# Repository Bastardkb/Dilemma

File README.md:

---

The Dilemma is a vertical stagger low-profile keyboard with mods.

## Table of contents

- [Features](#features)
- [Versions](#versions)
- [Required components](#required-components)
  - [3d prints - cases](#3d-prints---cases)
  - [Electronics](#electronics)
  - [Procyon mod](#procyon-mod)
  - [Cirque Trackpad mod](#cirque-trackpad-mod)
  - [Cases](#cases)
    - [Acrylic midplate (v2 only)](#acrylic-midplate-v2-only)
  - [Metal plates](#metal-plates)
  - [Community mods](#community-mods)
  - [Build guide](#build-guide)
  - [Forks](#forks)

---

# Features

- heavy pinky stagger
- MX and choc compatible
- version with hotswap
- underglow RGB, per-key RGB
- 2 Rotary encoders on thumb clusters
- connectors for OLED, LCD

# Versions

There are multiple versions of the dilemma:

| Folder          | Name                   | Size  | PCBA | Trackpad | Switches         | Additional features                          |
| --------------- | ---------------------- | ----- | ---- | -------- | ---------------- | -------------------------------------------- |
| `3x5_2`         | Dilemma DIY V2         | 3x5+2 | no   | Cirque   | MX, Choc V1      |                                              |
| `3x5_3`         | Dilemma V2             | 3x5+3 | yes  | Cirque   | MX, Choc V1      | Underglow, per-key RGB, rotary encoders      |
| `3x5_3_procyon` | Dilemma V3 hotswap     | 3x5+3 | yes  | Procyon  | Choc V1, hotswap | Underglow, per-key RGB, rotary encoders, VIK |
| `4x6_4`         | Dilemma MAX            | 4x6+4 | yes  | Cirque   | MX, Choc V1      | Underglow, per-key RGB, rotary encoders      |
| `4x6_4_procyon` | Dilemma MAX V3 hotswap | 4x6+4 | yes  | Procyon  | Choc V1, hotswap | Underglow, per-key RGB, rotary encodersk VIK |

# Required components

## 3d prints - cases

You can find the required 3d prints in the `mechanical` folder.

Most cases require a transparent mid layer to look good. You can either print it, or order it cut in acrylic.

## Electronics

The new revisions are made to be PCBA'd, you can find the gerber, BOM and POS files in the [Releases](https://github.com/bastardkb/dilemma/releases) section.

## Procyon mod

The `dilemma v3 hotswap` is made to work with a [Procyon PCB](https://github.com/bstiq/procyon).

## Cirque Trackpad mod

This mod uses I2C on the DIY version, and SPI on the assembled version.

The DIY version requires removing some resistors from the trackpad:

- R1
- R7 and R8 if you are using a microcontroller that runs on 5V

When installing the trackpad mod, you will need:

| Part name           | Amount | Link / source           |
| ------------------- | ------ | ----------------------- |
| M3 screw, torx, 6mm | 4      | Conrad                  |
| M3x5x5 screw insert | 4      | Aliexpress              |
| 3d printed parts    |        | See `mechanical` folder |
| 40mm cirque trackpad, curved    |        | |

If building the PCBA version, you will also need:

| Part name                                                     | Amount | Link / source |
| ------------------------------------------------------------- | ------ | ------------- |
| 12-position FPC cable, 0.5mm pitch, same side contacts, 100mm, type-B | 1      | Farnell       |

If building the DIY version, you will also need:

| Part name               | Amount | Link / source |
| ----------------------- | ------ | ------------- |
| SOD123 Resistor, 5kOhms | 2      |               |
| Cables                  |        |               |

## Cases

### Acrylic midplate (v2 only)

This case is only compatible with the assembled_v2 version !

Add an underglow effect and a beautiful view into the PCB with those acrylic midplates.

## Metal plates

Optional metal plates enables the use of tripods through magsafe magnets.

Order the [metal plates](mechanical/plates/v2/bottom_metal.dxf) in 3mm thickness. The metal needs to be *magnetized* !
Grab the appropriate DXF from the matched folder.

You will need:

| Part name              | Amount | Details           |
| ---------------------- | ------ | ----------------- |
| Metal plates           | 2      | 3mm               |
| Tripods                | 2      | Neewer Z flex     |
| Magsafe tripod adapter | 2      | Amazon/Aliexpress |

## Community mods

There are a range of community mods available (hex plates, covers...).

You can find more information in the readme in the `mechanical/community mods` folder.

## Build guide

https://docs.bastardkb.com/bg_dilemma/intro.html

## Forks

- [3x6 version](https://github.com/bstiq/Dilemma_3x6/)
- [3x5 + 3 version](https://github.com/dixls/Dilemma-3mod)

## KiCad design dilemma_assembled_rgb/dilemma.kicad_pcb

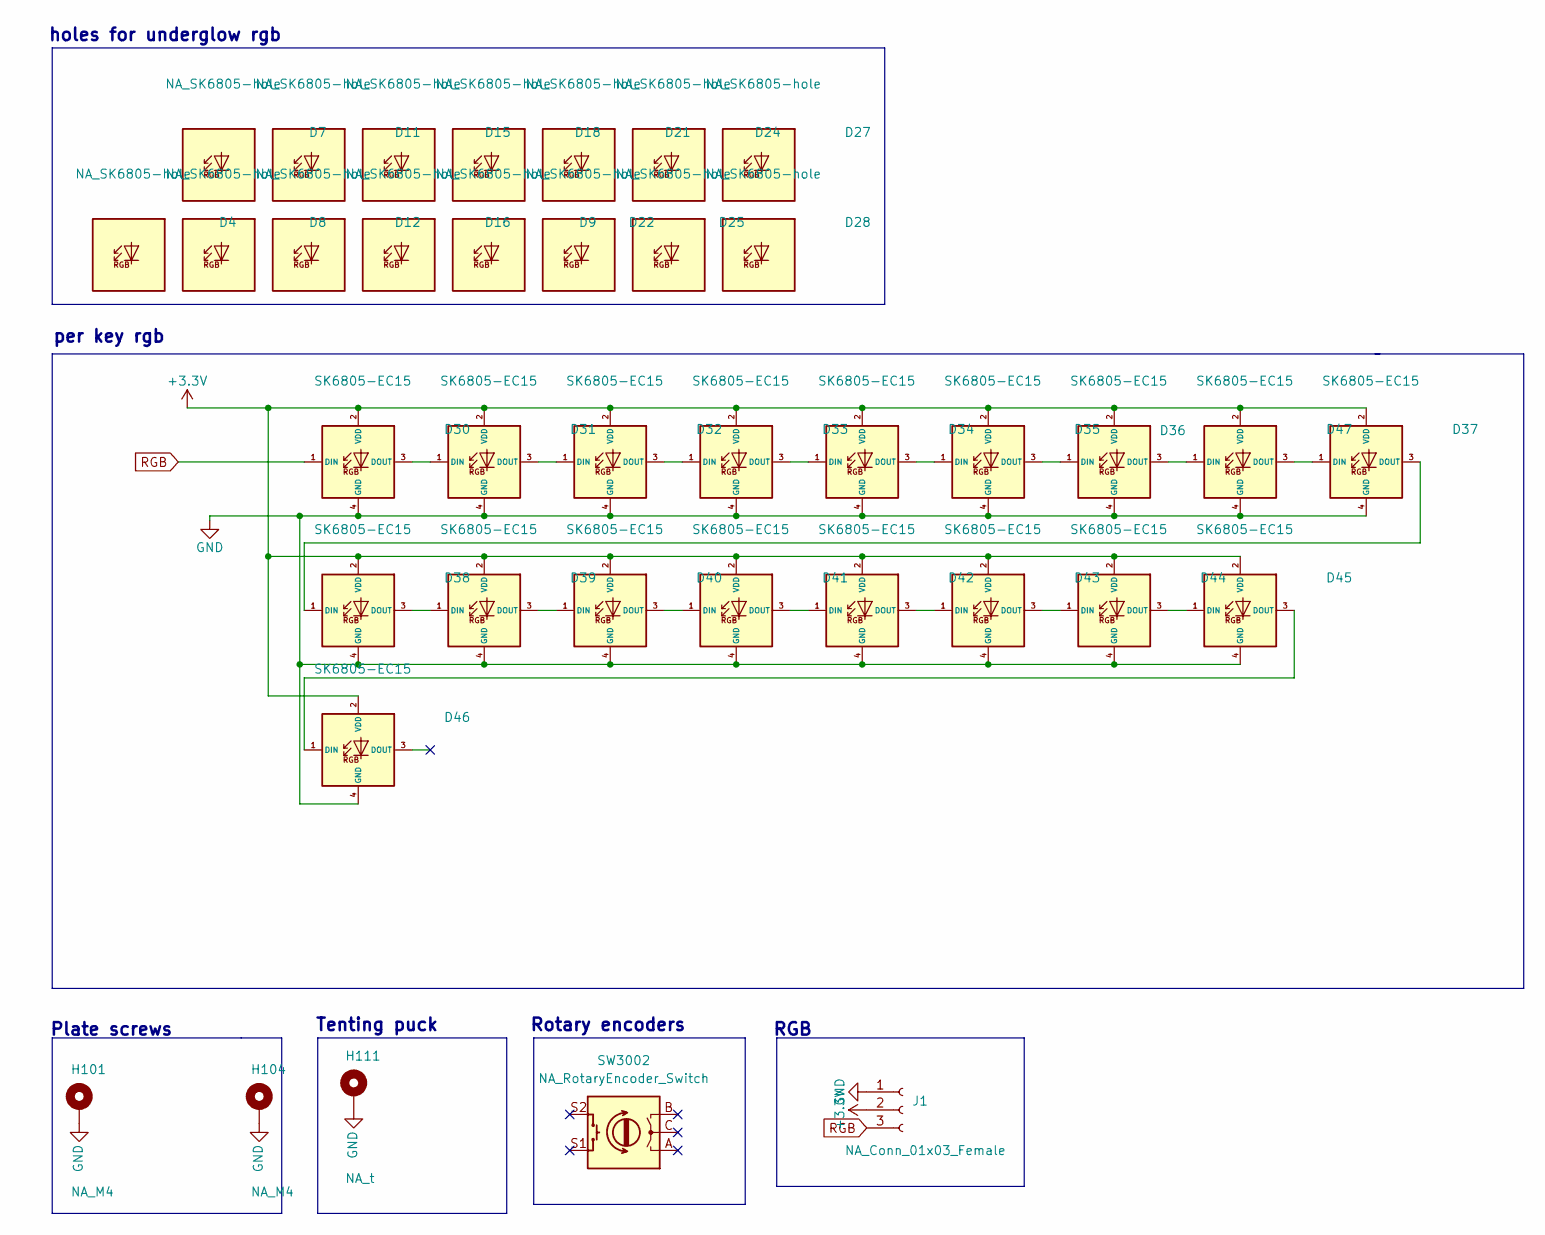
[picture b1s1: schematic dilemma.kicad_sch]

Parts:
D4, D7, D8, D21, D22, D24, D25, D27, D28: NA_SK6805-hole; LED_SK6805-EC15_1.5x1.5mm_P0.6mm_handsolder; MPN SK6805-EC15; LCSC C2890035
D9, D11, D12, D15, D16, D18: NA_SK6805-hole; LED_SK6805-EC15_hole; MPN SK6805-EC15; LCSC C2890035
D30, D31, D32, D33, D34, D35, D36, D37, D38, D39, D40, D41, D42, D43, D44, D45, D46, D47: SK6805-EC15; LED_SK6805-EC15_withSwitch; MPN SK6805-EC15; LCSC C2890035
H101, H104: NA_M4; MountingHole_3mm_Pad_hole
H111: NA_t; Tenting_Puck
J1: NA_Conn_01x03_Female; PinHeader_1x03_P2.54mm_Vertical_smd
SW3002: NA_RotaryEncoder_Switch; RotaryEncoder_Alps_EC11E-Switch_Vertical_H20mm_holes

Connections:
+3V3: D30.2 (VDD), D31.2 (VDD), D32.2 (VDD), D33.2 (VDD), D34.2 (VDD), D35.2 (VDD), D36.2 (VDD), D37.2 (VDD), D38.2 (VDD), D39.2 (VDD), D40.2 (VDD), D41.2 (VDD), D42.2 (VDD), D43.2 (VDD), D44.2 (VDD), D45.2 (VDD), D46.2 (VDD), D47.2 (VDD), J1.2
GND: D30.4 (GND), D31.4 (GND), D32.4 (GND), D33.4 (GND), D34.4 (GND), D35.4 (GND), D36.4 (GND), D37.4 (GND), D38.4 (GND), D39.4 (GND), D40.4 (GND), D41.4 (GND), D42.4 (GND), D43.4 (GND), D44.4 (GND), D45.4 (GND), D46.4 (GND), D47.4 (GND), H101.1, H104.1, H111.1, J1.1
unnamed: D30.3 (DOUT), D31.1 (DIN)
unnamed: D31.3 (DOUT), D32.1 (DIN)
unnamed: D32.3 (DOUT), D33.1 (DIN)
unnamed: D33.3 (DOUT), D34.1 (DIN)
unnamed: D34.3 (DOUT), D35.1 (DIN)
unnamed: D35.3 (DOUT), D36.1 (DIN)
unnamed: D36.3 (DOUT), D47.1 (DIN)
unnamed: D37.1 (DIN), D47.3 (DOUT)
unnamed: D37.3 (DOUT), D38.1 (DIN)
unnamed: D38.3 (DOUT), D39.1 (DIN)
unnamed: D39.3 (DOUT), D40.1 (DIN)
unnamed: D40.3 (DOUT), D41.1 (DIN)
unnamed: D41.3 (DOUT), D42.1 (DIN)
unnamed: D42.3 (DOUT), D43.1 (DIN)
unnamed: D43.3 (DOUT), D44.1 (DIN)
unnamed: D44.3 (DOUT), D45.1 (DIN)
unnamed: D45.3 (DOUT), D46.1 (DIN)
RGB: D30.1 (DIN), J1.3

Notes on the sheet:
per key rgb
Rotary encoders
RGB
holes for underglow rgb
Tenting puck
Plate screws

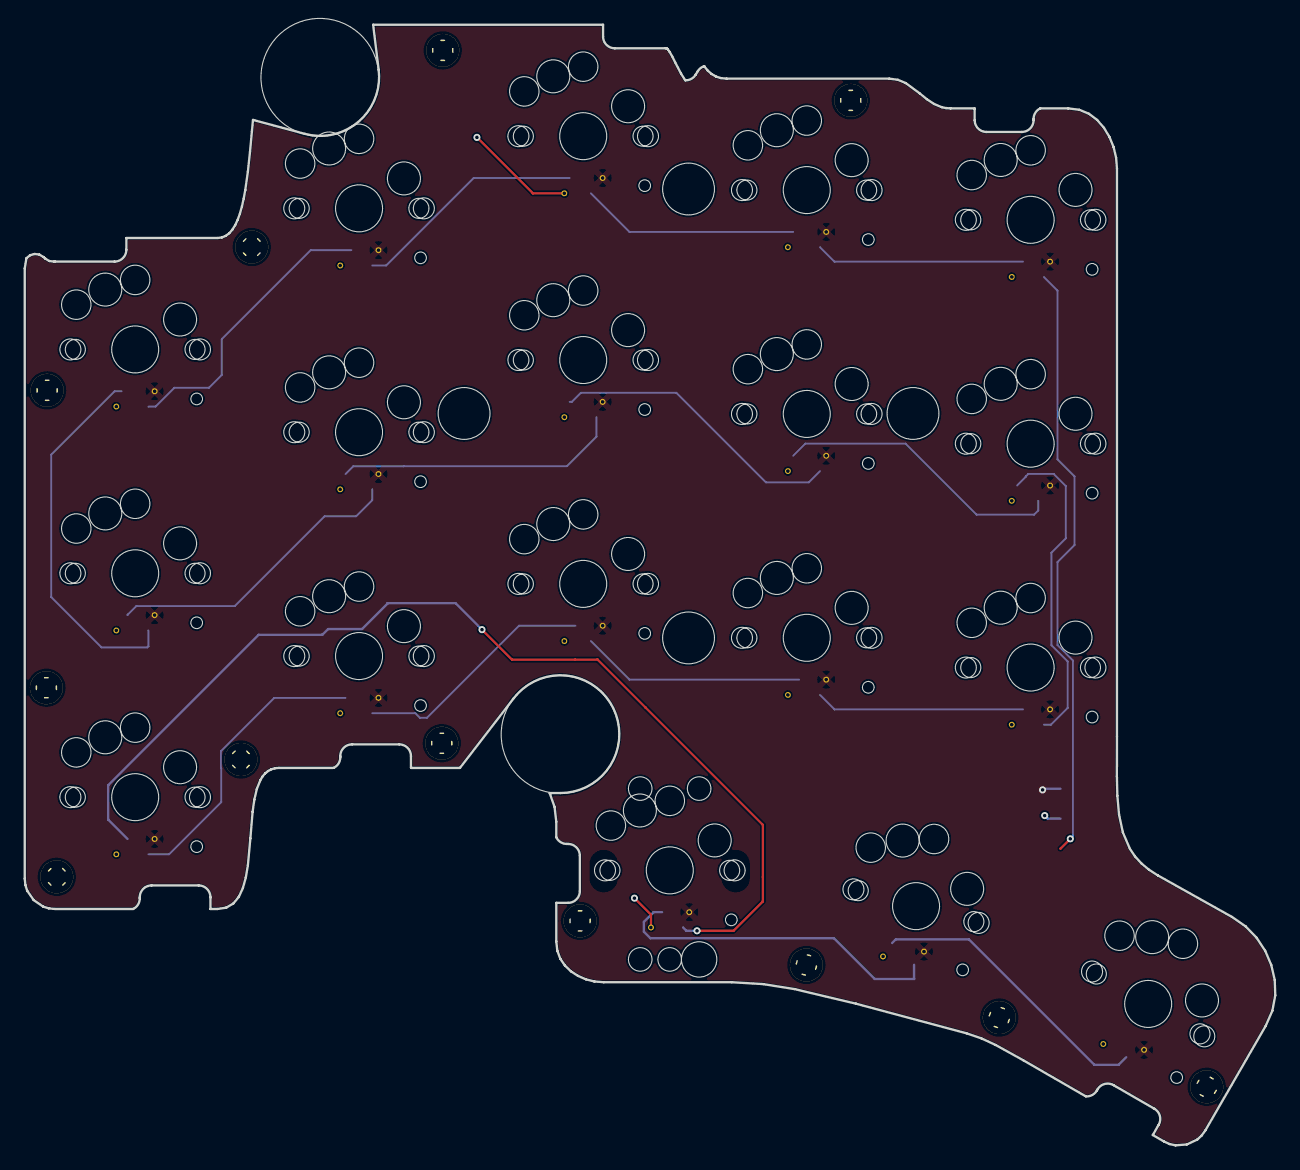
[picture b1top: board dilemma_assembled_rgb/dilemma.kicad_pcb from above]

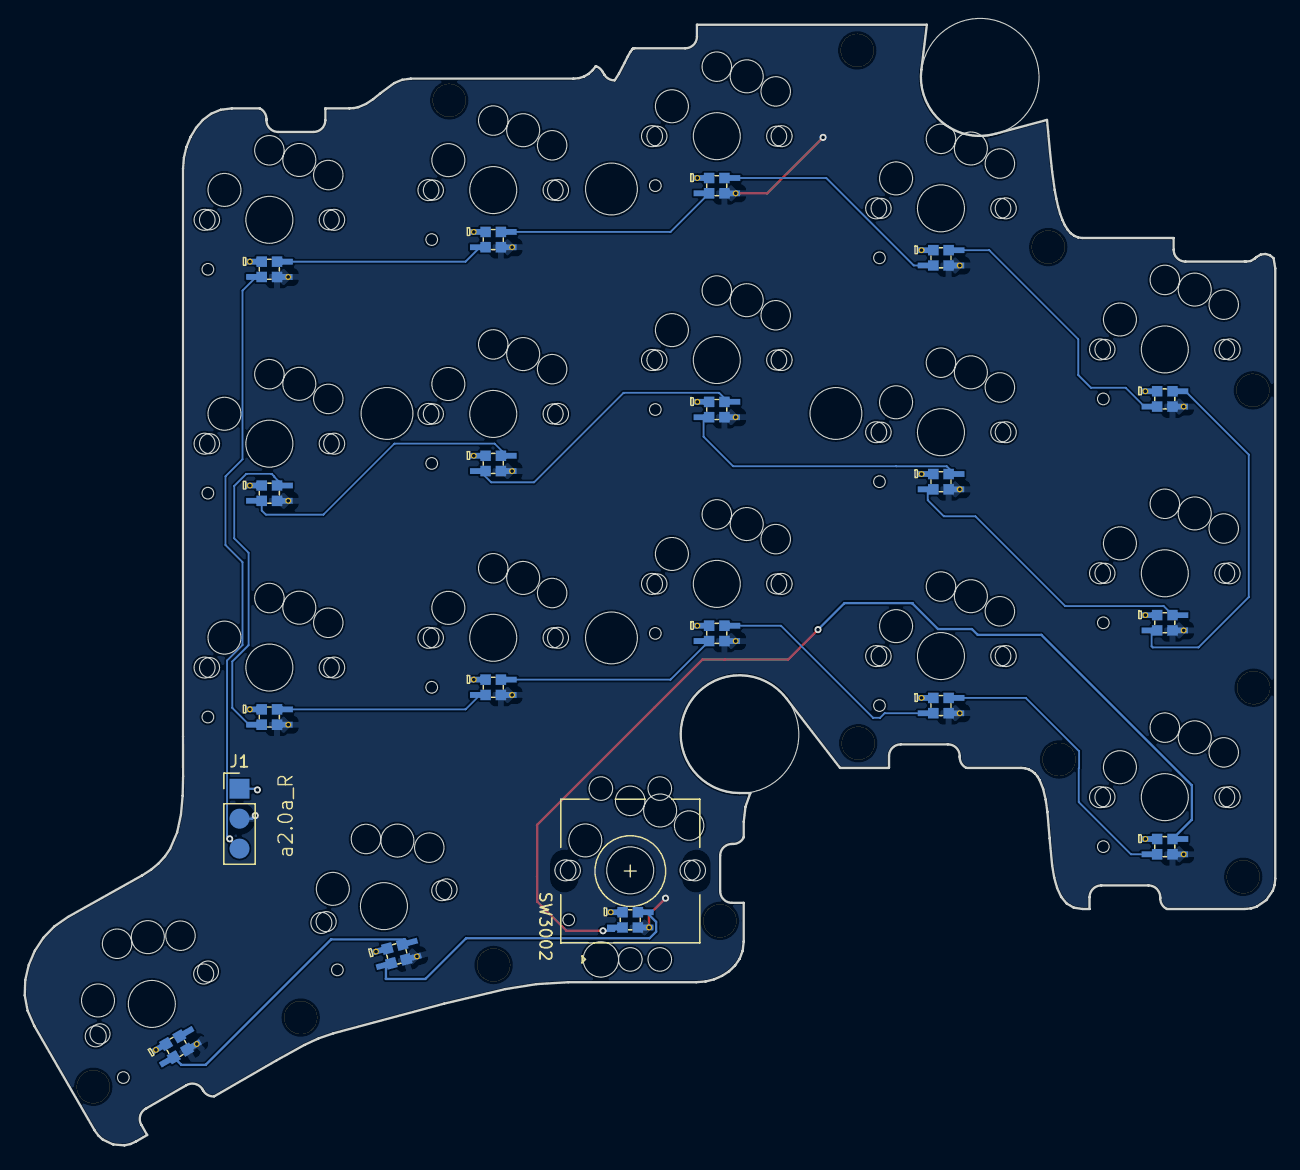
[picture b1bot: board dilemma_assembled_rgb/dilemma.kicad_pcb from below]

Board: 2 copper layers, 106.1 x 95.1 mm, 35 parts (20 on the bottom side), 20 nets.

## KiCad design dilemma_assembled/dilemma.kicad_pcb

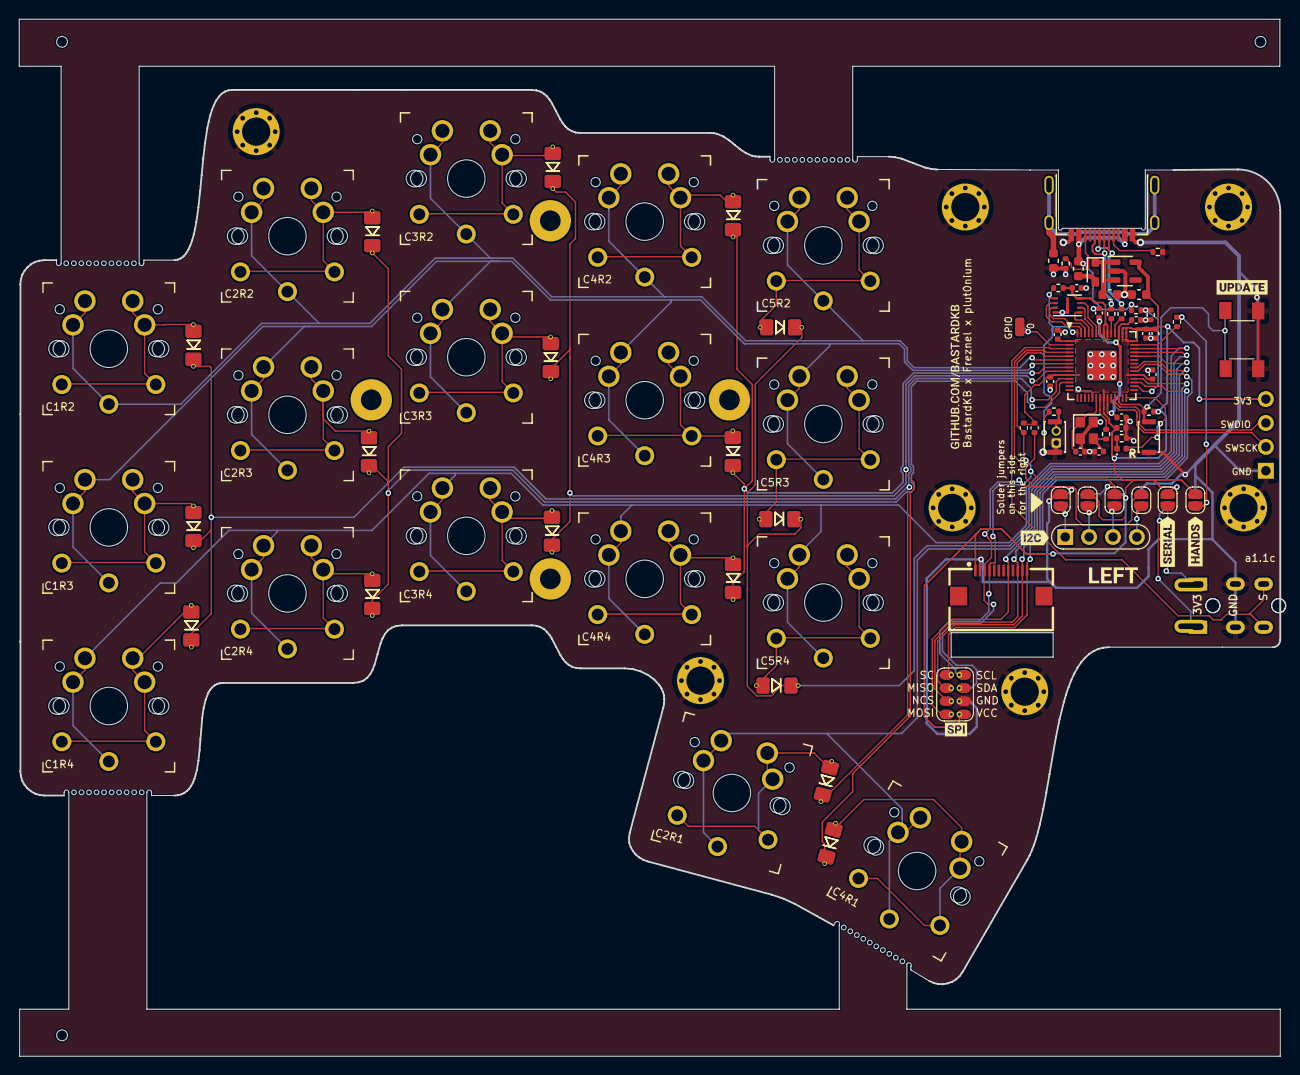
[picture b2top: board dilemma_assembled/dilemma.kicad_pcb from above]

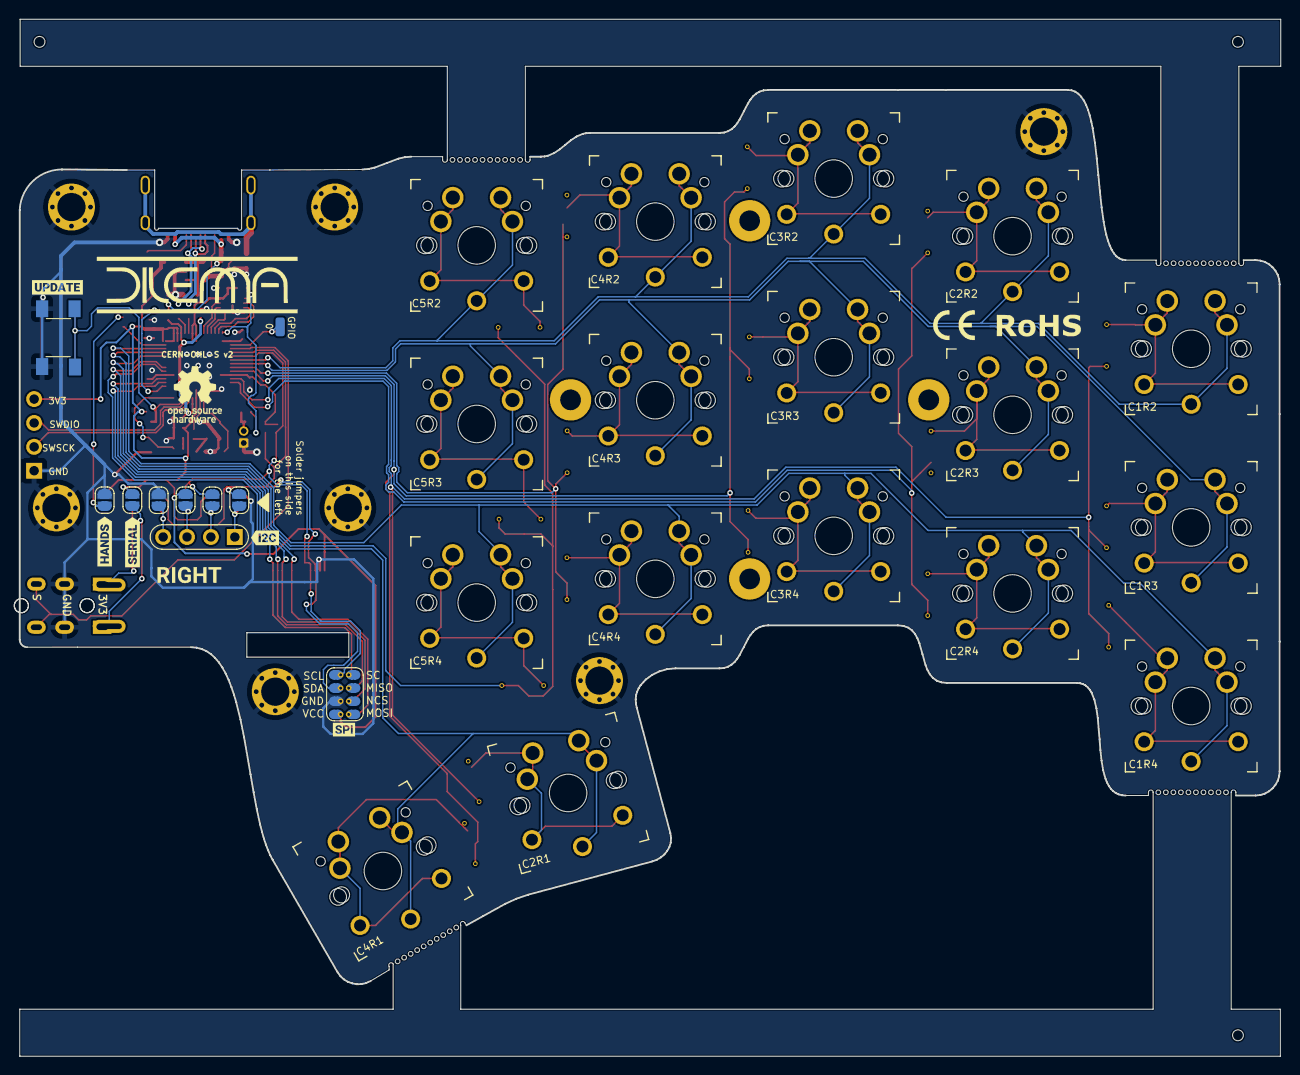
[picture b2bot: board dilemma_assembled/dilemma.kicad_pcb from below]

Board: 2 copper layers, 134.1 x 110.3 mm, 119 parts (15 on the bottom side), 71 nets.

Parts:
C1, C2: 1µ; C_0603_1608Metric
C3, C4: 15p; C_0402_1005Metric
C5, C6: 1µ; C_0402_1005Metric
C7, C8, C9, C10, C11, C12, C13, C14: 100n; C_0402_1005Metric
D1: LED; LED_0402_1005Metric
D2: B5817; D_SOD-323
D101, D102, D103, D104, D105, D106, D107, D108, D109, D110, D111, D112, D113, D114, D115, D116, D117: D; D_1206_handsolder_reversible
F1: Polyfuse; Fuse_0603_1608Metric
FB1: FerriteBead_Small; L_0603_1608Metric
H101, H102, H104, H105, H106, H107, H108: M4; MountingHole_3mm_Pad_Via
H103, H109, H110: t; JLC_SMT_Assembly_Hole
J1: USB_C_Receptacle_USB2.0; USB_C_Receptacle_HRO_TYPE-C-31-M-13B
J5: Conn_01x02; PinHeader_1x02_P1.27mm_Vertical
J102, J103: Serial; Jack_3.5mm_PJ320E_Horizontal_custom
J105: Conn_01x04_Female; PinHeader_1x04_P2.54mm_Vertical_debug
J107: Conn_01x08_Female; 1x08 smd reversible
J108, J109: Conn_01x01_Female; SolderWirePad_1x01_SMD_1x2mm
J113: Cirque; FPC-SMD_FPC05012-09200-.5mm
JP101, JP102, JP103, JP104, JP105, JP106, JP107, JP108, JP109, JP110, JP111, JP112: Jumper_2_Open; SolderJumper-2_P1.3mm_Open_RoundedPad1.0x1.5mm
O101: OLED; PinHeader_1x04_P2.54mm_Vertical
R1, R3, R8: 1k; R_0402_1005Metric
R2, R9, R11: 10k; R_0402_1005Metric
R4, R5, R10: 5.1k; R_0402_1005Metric
R6, R7: 27; R_0402_1005Metric
R101: 5.1k; R_0402_1005Metric_nolabel
R103, R104: 4.7k; R_0402_1005Metric_nolabel
SW1, SW2: SW_Push; SW_SPST_CK_KXT3
SW101, SW102, SW103, SW104, SW105, SW106, SW107, SW108, SW109, SW112, SW113, SW114, SW115, SW116, SW117, SW118: SW_Push; SW_MX_choc
SW110, SW111: SW_SPST; SW_Push_1P1T_NO_6x6mm_H9.5mm
SW119: locked; SW_MX_choc
U1: RP2040; QFN-56-1EP_7x7mm_P0.4mm_EP3.2x3.2mm
U2: GD25Q80CEIGR; USON-8-1EP_3x2mm_P0.5mm_EP0.25x1.65mm
U3: XC6210B332MR-G; SOT-23-5
Y1: Crystal_GND24; Crystal_SMD_2520-4Pin_2.5x2.0mm
kibuzzard-61F01A92: G***; kibuzzard-61F01A92
kibuzzard-62C1A775, kibuzzard-62C1A775#2: G***; kibuzzard-62C1A775
kibuzzard-62C19A64, kibuzzard-62C19A64#2: G***; kibuzzard-62C19A64
kibuzzard-62C19AB4: G***; kibuzzard-62C19AB4
kibuzzard-62C19AC2: G***; kibuzzard-62C19AC2
kibuzzard-62C19AE7, kibuzzard-62C19AE7#2: G***; kibuzzard-62C19AE7
kibuzzard-62C55DF6, kibuzzard-62C55DF6#2: G***; kibuzzard-62C55DF6
kibuzzard-62C547B3: G***; kibuzzard-62C547B3
kibuzzard-62C5480E: G***; kibuzzard-62C5480E

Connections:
+1V1: C6.1, C7.1, C8.1, U1.23 (DVDD), U1.45 (VREG_VOUT), U1.50 (DVDD)
+3V3: C2.1, C5.1, C9.1, C10.1, C11.1, C12.1, C13.1, C14.1, J105.1, J107.1, J113.1, JP101.2 (B), JP102.2 (B), JP107.1 (A), JP108.1 (A), JP112.2 (B), R2.2, R9.2, R103.2, R104.1, U1.1 (IOVDD), U1.10 (IOVDD), U1.22 (IOVDD), U1.33 (IOVDD), U1.42 (IOVDD), U1.43 (ADC_AVDD), U1.44 (VREG_IN), U1.48 (USB_VDD), U1.49 (IOVDD), U2.8 (VCC), U3.5 (VOUT)
/D+: J1.A6 (D+), J1.B6 (D+), R6.1
/D-: J1.A7 (D-), J1.B7 (D-), R7.1
/LED: D1.2 (A), U1.28 (GPIO17)
/QSPI_D0: U1.53 (QSPI_SD0), U2.5 (DI(IO0))
/QSPI_D1: U1.55 (QSPI_SD1), U2.2 (DO(IO1))
/QSPI_D2: U1.54 (QSPI_SD2), U2.3 (IO2)
/QSPI_D3: U1.51 (QSPI_SD3), U2.7 (IO3)
/QSPI_SCLK: U1.52 (QSPI_SCLK), U2.6 (CLK)
/QSPI_~CS: R3.2, R9.1, U1.56 (QSPI_SS), U2.1 (~CS)
/SWCLK: J105.3, U1.24 (SWCLK)
/SWD: J105.2, U1.25 (SWD)
/VBUS_DET: R10.1, R11.2, U1.30 (GPIO19)
Gnd_l: C1.2, C2.2, C3.2, C4.2, C5.2, C6.2, C7.2, C8.2, C9.2, C10.2, C11.2, C12.2, C13.2, C14.2, FB1.1, H101.1, H102.1, H104.1, H105.1, H106.1, H107.1, H108.1, J1.A1 (GND), J1.A12 (GND), J1.B1 (GND), J1.B12 (GND), J5.1, J102.R1, J103.R1, J105.4, J107.2, J113.2, JP109.1 (A), JP110.1 (A), JP111.2 (B), R1.1, R4.1, R5.1, R11.1, SW1.1, SW2.1, SW110.2 (B), SW111.2 (B), U1.19 (TESTEN), U1.57 (GND), U2.4 (GND), U2.9 (EP), U3.2 (GND), Y1.2, Y1.4
NCS: J107.6, J113.10, U1.32 (GPIO21)
unnamed: C3.1, U1.20 (XIN), Y1.1
unnamed: C4.1, R8.1, Y1.3
unnamed: D1.1 (K), R1.2
unnamed: D2.2 (A), F1.2
unnamed: D101.2 (A), SW101.2
unnamed: D102.2 (A), SW102.2
unnamed: D103.2 (A), SW103.2
unnamed: D104.2 (A), SW104.2
unnamed: D105.2 (A), SW105.2
unnamed: D106.2 (A), SW106.2
unnamed: D107.2 (A), SW107.2
unnamed: D108.2 (A), SW108.2
unnamed: D109.2 (A), SW109.2
unnamed: D110.2 (A), SW112.2
unnamed: D111.2 (A), SW113.2
unnamed: D112.2 (A), SW114.2
unnamed: D113.2 (A), SW115.2
unnamed: D114.2 (A), SW116.2
unnamed: D115.2 (A), SW117.2
unnamed: D116.2 (A), SW118.2
unnamed: D117.2 (A), SW119.2
unnamed: FB1.2, J1.S1 (SHIELD)
unnamed: J1.A5 (CC1), R4.2
unnamed: J1.B5 (CC2), R5.2
unnamed: J5.2, R3.1, SW2.2
unnamed: J102.T, JP101.1 (A)
unnamed: J103.T, JP102.1 (A)
unnamed: JP103.2 (B), JP110.2 (B), O101.1
unnamed: JP104.2 (B), JP109.2 (B), O101.4
unnamed: JP105.2 (B), JP108.2 (B), O101.2
unnamed: JP106.2 (B), JP107.2 (B), O101.3
unnamed: JP111.1 (A), JP112.1 (A), R101.2
unnamed: R6.2, U1.47 (USB_DP)
unnamed: R7.2, U1.46 (USB_DM)
unnamed: R8.2, U1.21 (XOUT)
Rst_l: R2.1, SW1.2, SW110.1 (A), SW111.1 (A), U1.26 (RUN/~RST)
VBUS: F1.1, J1.A4 (VBUS), J1.A9 (VBUS), J1.B4 (VBUS), J1.B9 (VBUS), R10.2
bat_l: C1.1, D2.1 (K), U3.1 (VIN), U3.3 (EN)
col1_l: D101.1 (K), D102.1 (K), D103.1 (K), D116.1 (K), U1.11 (GPIO8)
col2_l: D104.1 (K), D105.1 (K), D106.1 (K), U1.12 (GPIO9)
col3_l: D107.1 (K), D108.1 (K), D109.1 (K), D117.1 (K), U1.9 (GPIO7)
col4_l: D110.1 (K), D111.1 (K), D112.1 (K), U1.8 (GPIO6)
col5_l: D113.1 (K), D114.1 (K), D115.1 (K), U1.39 (GPIO27_ADC1)
hand: R101.1, U1.41 (GPIO29_ADC3)
miso_l: J107.7, J113.11, U1.31 (GPIO20)
mosi_l: J107.5, J113.8, U1.35 (GPIO23)
rgb_l: J108.1, J109.1, U1.2 (GPIO0)
row1_l: SW118.1, SW119.1, U1.38 (GPIO26_ADC0)
row2_l: SW101.1, SW104.1, SW107.1, SW112.1, SW115.1, U1.6 (GPIO4)
row3_l: SW102.1, SW105.1, SW108.1, SW113.1, SW116.1, U1.7 (GPIO5)
row4_l: SW103.1, SW106.1, SW109.1, SW114.1, SW117.1, U1.40 (GPIO28_ADC2)
sc_l: J107.8, J113.12, U1.34 (GPIO22)
scl_l: J107.4, J113.4, JP105.1 (A), JP106.1 (A), R104.2, U1.5 (GPIO3)
sda_l: J107.3, J113.3, JP103.1 (A), JP104.1 (A), R103.1, U1.4 (GPIO2)
serial_l: J102.R2, J103.R2, U1.3 (GPIO1)

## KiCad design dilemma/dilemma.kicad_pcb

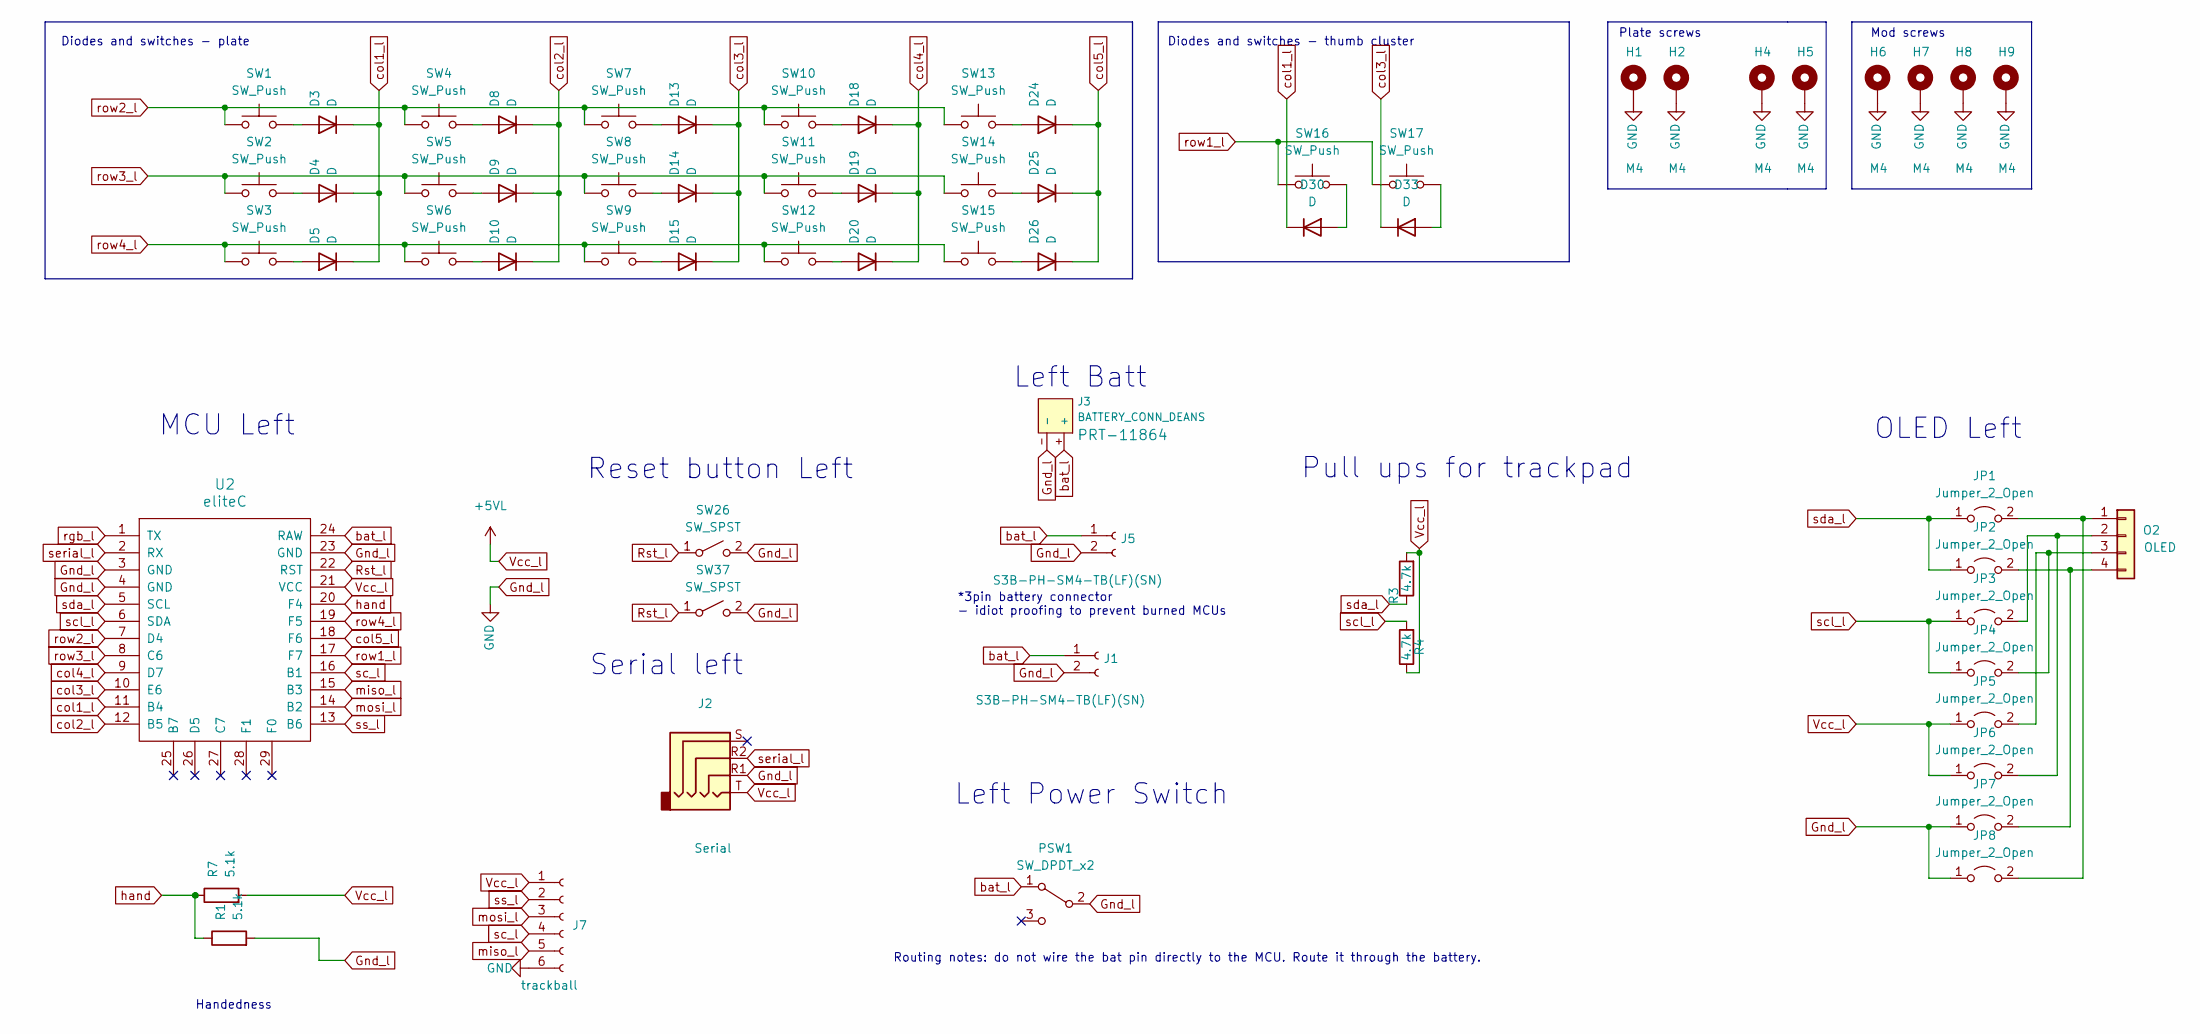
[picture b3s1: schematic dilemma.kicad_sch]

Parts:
D3, D4, D5, D8, D9, D10, D13, D14, D15, D18, D19, D20, D24, D25, D26, D30, D33: D; D_1206_handsolder_reversible
H1, H2, H4, H5, H6, H7, H8, H9: M4; MountingHole_3mm_Pad_thin
J1, J5: S3B-PH-SM4-TB(LF)(SN); JST_SH_BM02B-SRSS-TB_1x02-1MP_P1.00mm_Vertical; LCSC C265101
J2: Serial; Jack_3.5mm_PJ320E_Horizontal_reversible
J3: BATTERY_CONN_DEANS; battery_connector_THT
J7: trackball; 6_PinHeader
JP1, JP2, JP3, JP4, JP5, JP6, JP7, JP8: Jumper_2_Open; SolderJumper-2_P1.3mm_Open_RoundedPad1.0x1.5mm
O2: OLED; PinHeader_1x04_P2.54mm_Vertical
PSW1: SW_DPDT_x2; Switch_MSK-12C01-07; LCSC C431540
R1, R7: 5.1k; R_1206_handsolder; JLCPCB BOM 1
R3, R4: 4.7k; R_1206_handsolder_reversible; LCSC C269746
SW1, SW2, SW3, SW4, SW5, SW6, SW7, SW8, SW9, SW10, SW11, SW12, SW13, SW14, SW15, SW16, SW17: SW_Push; SW_MX_choc
SW26, SW37: SW_SPST; SW_Push_1P1T_NO_6x6mm_H9.5mm
U2: eliteC; pro-micro

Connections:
unnamed: D3.2 (A), SW1.2
unnamed: D4.2 (A), SW2.2
unnamed: D5.2 (A), SW3.2
unnamed: D8.2 (A), SW4.2
unnamed: D9.2 (A), SW5.2
unnamed: D10.2 (A), SW6.2
unnamed: D13.2 (A), SW7.2
unnamed: D14.2 (A), SW8.2
unnamed: D15.2 (A), SW9.2
unnamed: D18.2 (A), SW10.2
unnamed: D19.2 (A), SW11.2
unnamed: D20.2 (A), SW12.2
unnamed: D24.2 (A), SW13.2
unnamed: D25.2 (A), SW14.2
unnamed: D26.2 (A), SW15.2
unnamed: D30.2 (A), SW16.2
unnamed: D33.2 (A), SW17.2
unnamed: JP1.2 (B), JP8.2 (B), O2.1
unnamed: JP2.2 (B), JP7.2 (B), O2.4
unnamed: JP3.2 (B), JP6.2 (B), O2.2
unnamed: JP4.2 (B), JP5.2 (B), O2.3
Rst_l: SW26.1 (A), SW37.1 (A), U2.22 (RST)
Vcc_l: J2.T, J7.1, JP5.1 (A), JP6.1 (A), R3.2, R4.1, R7.2, U2.21 (VCC)
col1_l: D3.1 (K), D4.1 (K), D5.1 (K), D30.1 (K), U2.11 (B4)
col2_l: D8.1 (K), D9.1 (K), D10.1 (K), U2.12 (B5)
col3_l: D13.1 (K), D14.1 (K), D15.1 (K), D33.1 (K), U2.10 (E6)
col4_l: D18.1 (K), D19.1 (K), D20.1 (K), U2.9 (D7)
col5_l: D24.1 (K), D25.1 (K), D26.1 (K), U2.18 (F6)
hand: R1.1, R7.1, U2.20 (F4)
miso_l: J7.5, U2.15 (B3)
mosi_l: J7.3, U2.14 (B2)
rgb_l: U2.1 (TX)
row1_l: SW16.1, SW17.1, U2.17 (F7)
row2_l: SW1.1, SW4.1, SW7.1, SW10.1, SW13.1, U2.7 (D4)
row3_l: SW2.1, SW5.1, SW8.1, SW11.1, SW14.1, U2.8 (C6)
row4_l: SW3.1, SW6.1, SW9.1, SW12.1, SW15.1, U2.19 (F5)
sc_l: J7.4, U2.16 (B1)
scl_l: JP3.1 (A), JP4.1 (A), R4.2, U2.6 (SDA)
sda_l: JP1.1 (A), JP2.1 (A), R3.1, U2.5 (SCL)
serial_l: J2.R2, U2.2 (RX)
ss_l: J7.2, U2.13 (B6)

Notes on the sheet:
MCU Left
Left Batt
Handedness
Plate screws
Routing notes: do not wire the bat pin directly to the MCU. Route it through the battery.
Serial left
Diodes and switches - plate
Reset button Left
Pull ups for trackpad
Mod screws
Left Power Switch
OLED Left
Diodes and switches - thumb cluster
*3pin battery connector - idiot proofing to prevent burned MCUs

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
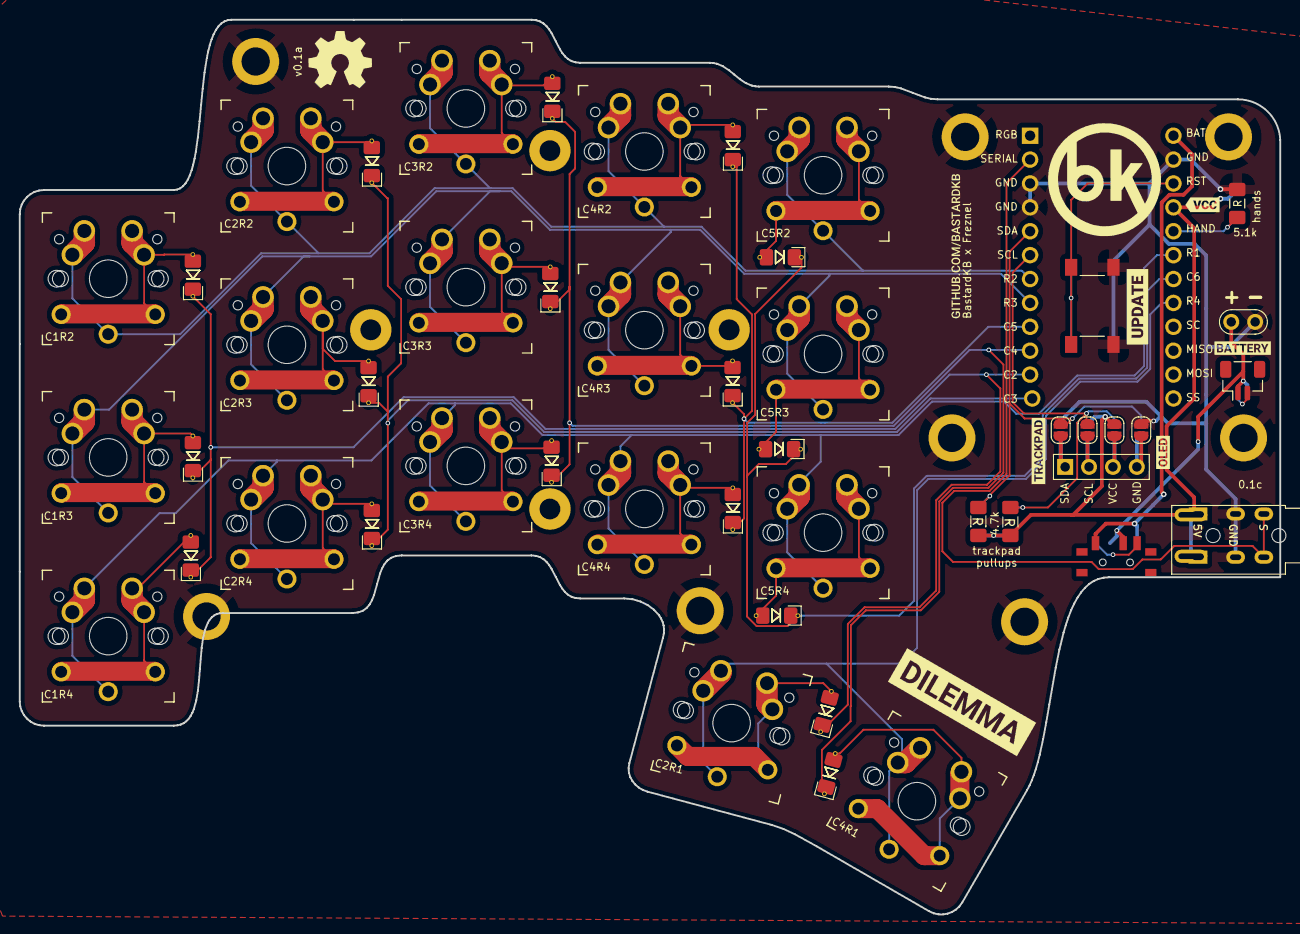
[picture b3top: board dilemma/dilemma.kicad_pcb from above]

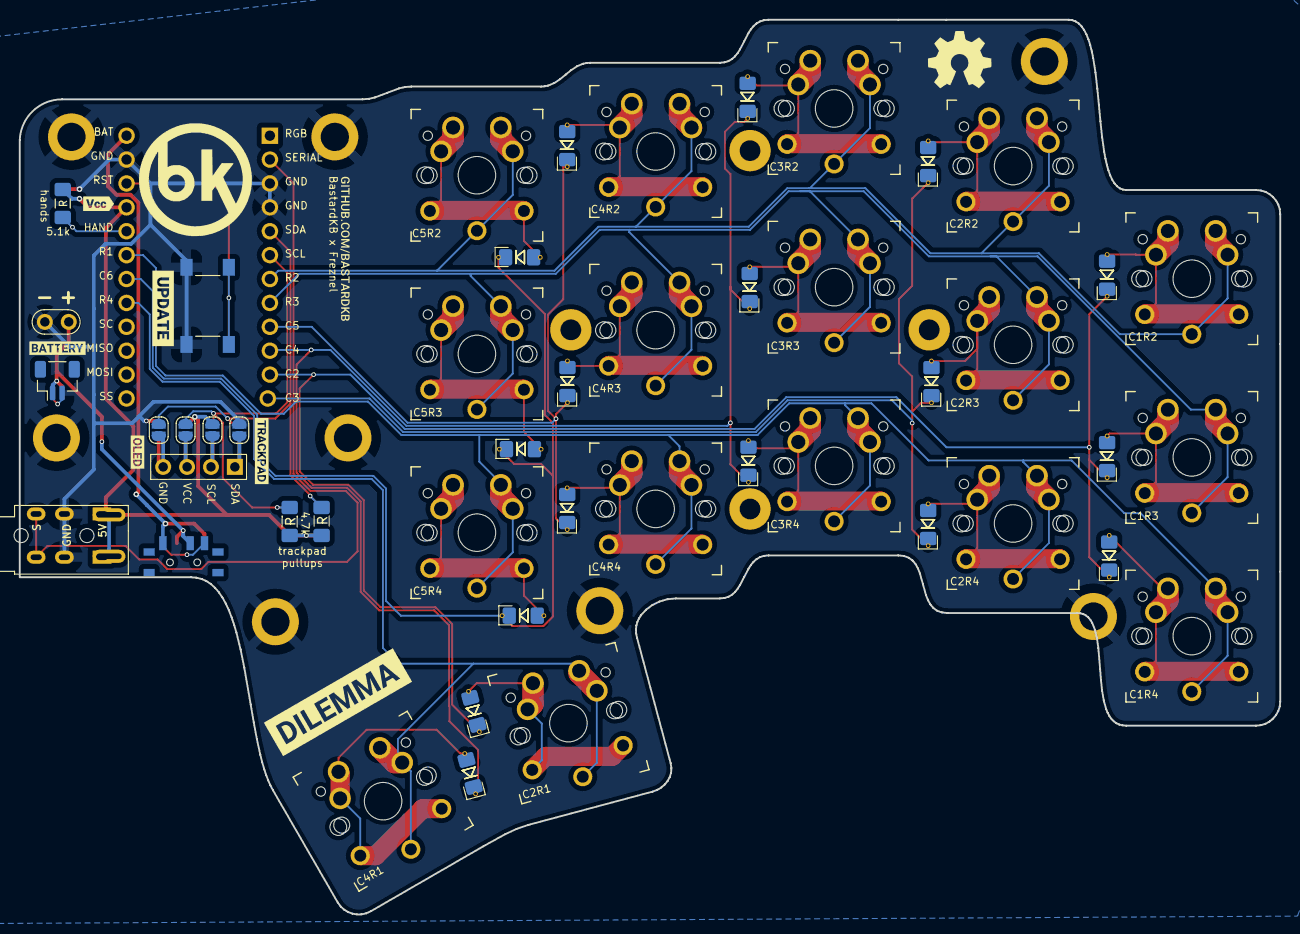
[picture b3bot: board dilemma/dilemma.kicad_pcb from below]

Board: 2 copper layers, 134.0 x 95.1 mm, 77 parts (15 on the bottom side), 39 nets.

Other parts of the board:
kibuzzard-61F01A92, kibuzzard-61F01A92#2: G***; kibuzzard-61F01A92
kibuzzard-61F01C84, kibuzzard-61F01C84#2: G***; kibuzzard-61F01C84
kibuzzard-628D3AA1: G***; kibuzzard-628D3AA1
kibuzzard-628D396A: G***; kibuzzard-628D396A
kibuzzard-628DFB5F, kibuzzard-628DFB5F#2: G***; kibuzzard-628DFB5F
kibuzzard-628DFB48, kibuzzard-628DFB48#2: G***; kibuzzard-628DFB48
kibuzzard-628DFB95, kibuzzard-628DFB95#2: G***; kibuzzard-628DFB95
kibuzzard-628E0199, kibuzzard-628E0199#2: G***; kibuzzard-628E0199

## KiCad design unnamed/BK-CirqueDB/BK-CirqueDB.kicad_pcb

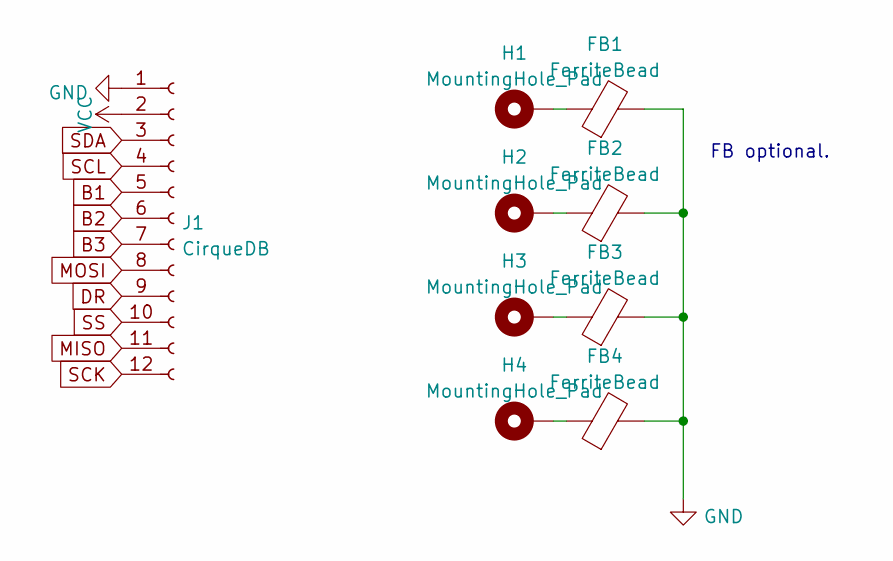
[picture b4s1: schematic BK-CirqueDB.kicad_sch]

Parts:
FB1, FB2, FB3, FB4: FerriteBead; L_0805_2012Metric_Pad1.15x1.40mm_HandSolder
H1, H2, H3, H4: MountingHole_Pad; MountingHole_3.2mm_M3_DIN965_Pad
J1: CirqueDB; CirqueDB-BK

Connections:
B1: J1.5
B2: J1.6
B3: J1.7
DR: J1.9
GND: FB1.2, FB2.2, FB3.2, FB4.2, J1.1
MISO: J1.11
MOSI: J1.8
unnamed: FB1.1, H1.1
unnamed: FB2.1, H2.1
unnamed: FB3.1, H3.1
unnamed: FB4.1, H4.1
SCK: J1.12
SCL: J1.4
SDA: J1.3
SS: J1.10
VCC: J1.2

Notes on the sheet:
FB optional.

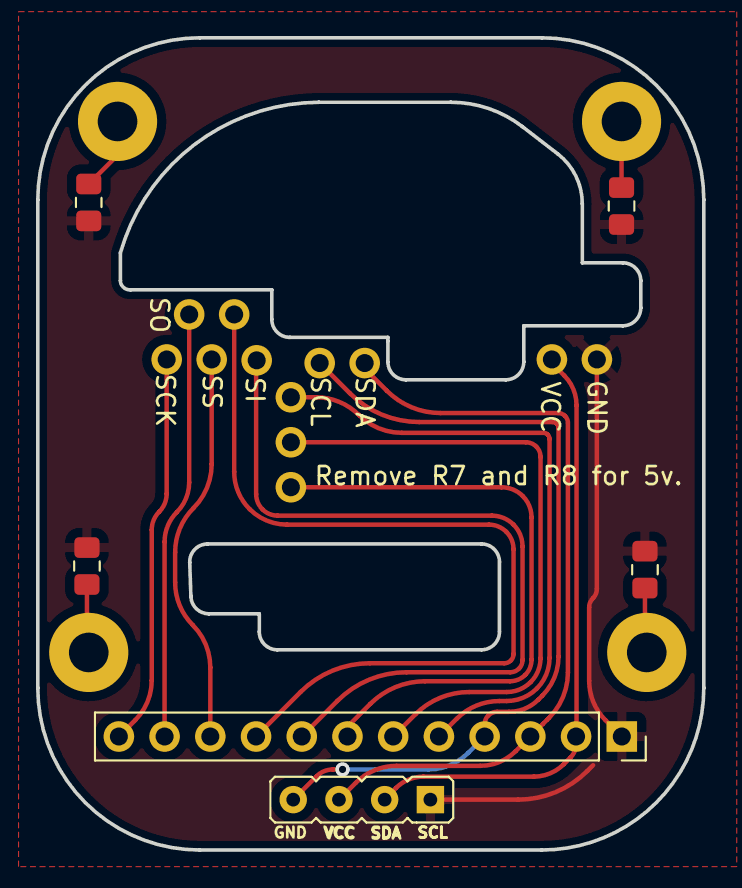
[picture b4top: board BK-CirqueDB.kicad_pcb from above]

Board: 2 copper layers, 37.0 x 45.1 mm, 9 parts (0 on the bottom side), 5 nets.

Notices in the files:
3x5_3/dilemma.kicad_sch:
Licensed under CERN-OHL-W v2
dilemma_assembled/dilemma.kicad_pcb:
CERN-OHL-S v2
